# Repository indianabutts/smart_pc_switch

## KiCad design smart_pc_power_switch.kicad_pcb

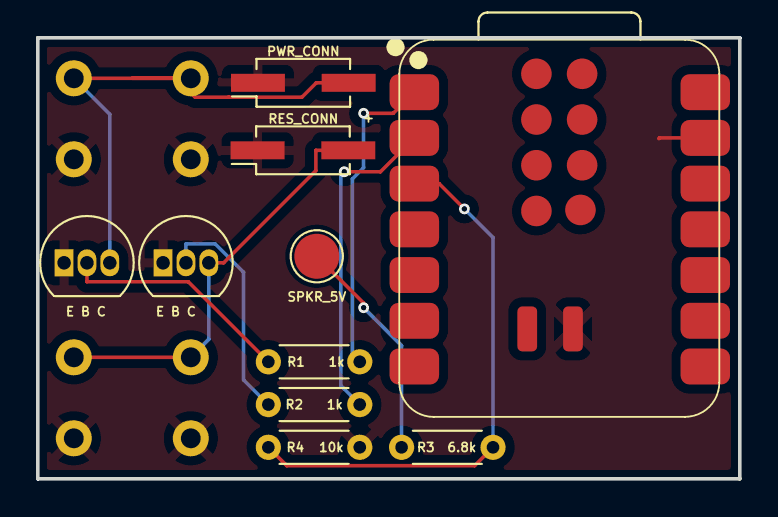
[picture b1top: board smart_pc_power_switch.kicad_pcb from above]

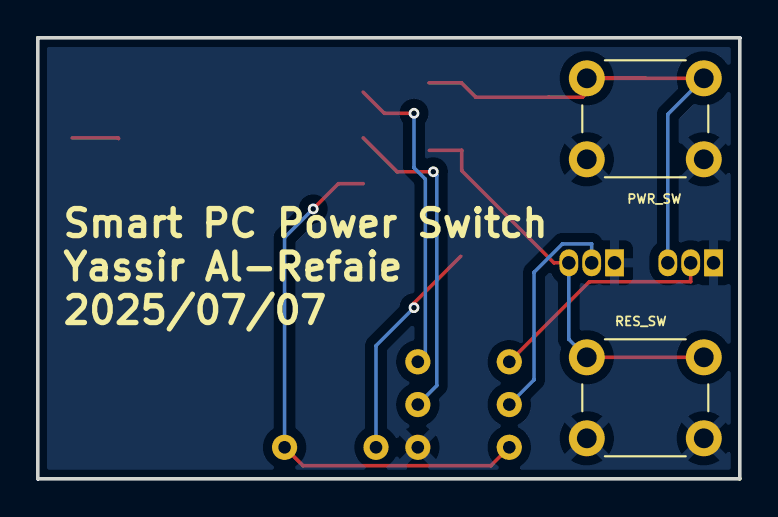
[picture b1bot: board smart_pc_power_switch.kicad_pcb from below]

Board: 2 copper layers, 39.0 x 24.5 mm, 12 parts (2 on the bottom side), 9 nets.

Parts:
J3: PWR_CONN; PinSocket_2x01_P2.54mm_Vertical_SMD
J4: RES_CONN; PinSocket_2x01_P2.54mm_Vertical_SMD
J5: SPKR_5V; TestPoint_Pad_D2.5mm
Q1, Q2: 2N3904; TO-92_Inline
R1, R2: 1k; R_Axial_DIN0204_L3.6mm_D1.6mm_P5.08mm_Horizontal
R3: 6.8k; R_Axial_DIN0204_L3.6mm_D1.6mm_P5.08mm_Horizontal
R4: 10k; R_Axial_DIN0204_L3.6mm_D1.6mm_P5.08mm_Horizontal
SW1: PWR_SW; SW_PUSH_6mm_H5mm
SW2: RES_SW; SW_PUSH_6mm_H5mm
U1: XIAO-ESP32-S3-SMD; XIAO-ESP32C6-SMD

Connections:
GPIO0: R1.1, U1.1 (GPIO0_A0_D0)
GPIO1: R2.1, U1.2 (GPIO1_A1_D1)
GPIO2: R3.1, R4.2, U1.3 (GPIO2_A2_D2)
unnamed: Q1.2 (B), R1.2
unnamed: Q2.2 (B), R2.2
PWR+: J3.2, Q1.3 (C), SW1.1
PWR-: J3.1, J4.1, Q1.1 (E), Q2.1 (E), R4.1, SW1.2, SW2.2, U1.13 (GND), U1.16 (GND)
RES+: J4.2, Q2.3 (C), SW2.1
SPKR_5V: J5.1, R3.2

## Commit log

2025-07-06 Initial version
2025-07-06 Power state correctly read
2025-07-06 Toggle Switch maintains state of the PC
2025-07-06 Add votlage divider for power sensor
2025-07-07 Initial PCB Drafted and Ordered
2025-07-07 Added 3D model for ESP32
2025-07-13 Add Force Shutdown
2025-07-13 Initial try at getting it discoverable
2025-07-13 Added URL to repo
2025-07-13 Fixed Conflict overzealous resolutio
2025-07-27 Uninverted GPIO
